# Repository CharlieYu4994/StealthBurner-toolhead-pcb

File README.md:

# StealthBurner-PCB
为 Voron Design 最新的 StealthBurner 设计的集线 PCB 板

在线 BOM 表：http://blog.charlie.moe/StealthBurner-toolhead-pcb/bom/bom

## 特点
+ 自带一个 NTC 3950 10K 的热敏电阻，可以用于测试仓温
+ 使用 StealthBurner 官方的固定孔位，可以无损兼容现有打印件
+ 使用 18 根线，比直连更省线材

## 使用

### 打样
使用「gerber」文件夹内的文件即可，建议使用 1mm 板厚，10mil 最小线宽

### 接线

1. 将 5v 连接到 LED 的 5v 电源，将 DATA 连接到 LED 信号引脚
2. 将 V_FAN 连接到你使用的风扇电源正极（两个风扇只能使用同一电压），将 PCF 和 HEF 连接到对应风扇负极
3. 将 +24v 连接到探头电源，将 P_SIG 连接到探头信号引脚
4. 将 GNDA 连接到测温接口的负极，将 CBT 和 HET 连接到对应侧温接口的正极（两个热敏电阻共地）
5. 将 A+/A-/B+/B- 连接到步进电机驱动
6. 将 HE+/HE- 连接到热端加热器接口

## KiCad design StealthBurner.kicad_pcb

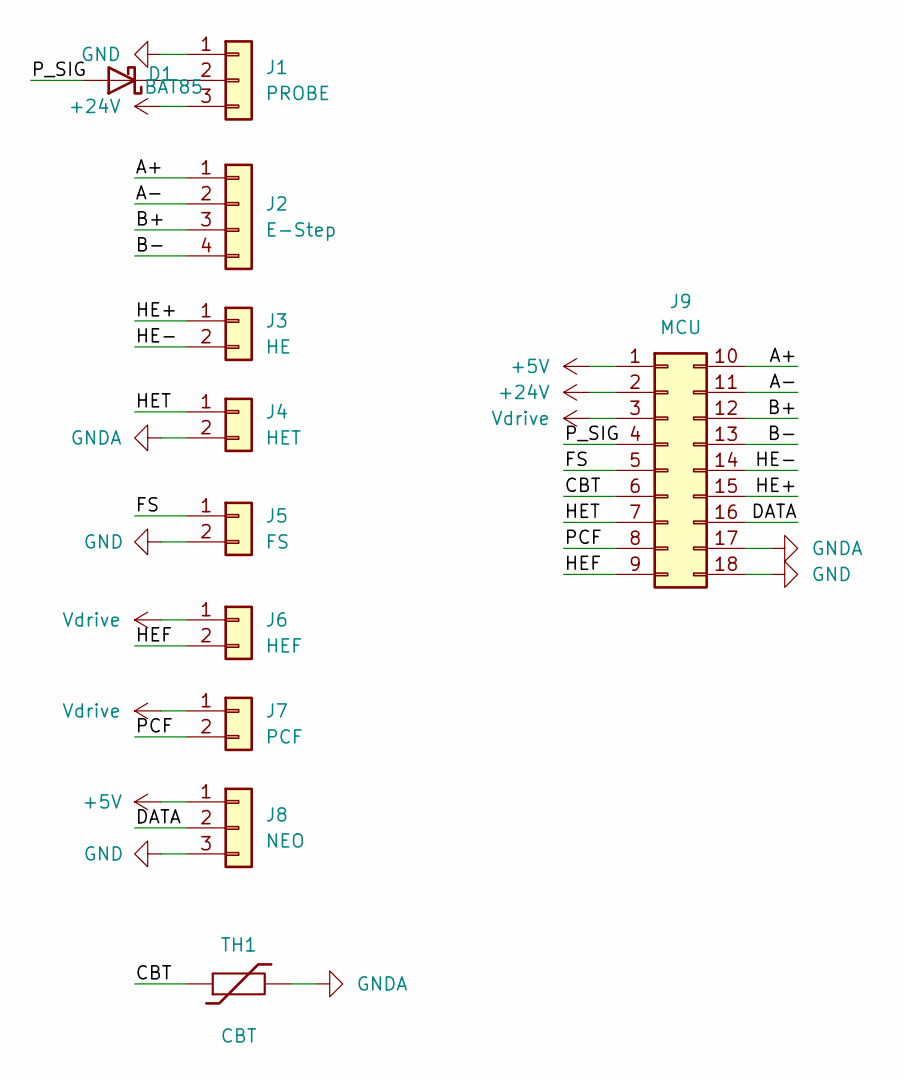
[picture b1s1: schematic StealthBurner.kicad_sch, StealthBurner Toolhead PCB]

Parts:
D1: BAT85; D_DO-35_SOD27_P2.54mm_Vertical_AnodeUp
J1: PROBE; JST_PH_B3B-PH-K_1x03_P2.00mm_Vertical
J2: E-Step; JST_PH_B4B-PH-K_1x04_P2.00mm_Vertical
J3: HE; Molex_Micro-Fit_3.0_43045-0200_2x01_P3.00mm_Horizontal
J4: HET; JST_PH_B2B-PH-K_1x02_P2.00mm_Vertical
J5: FS; JST_PH_B2B-PH-K_1x02_P2.00mm_Vertical
J6: HEF; JST_PH_B2B-PH-K_1x02_P2.00mm_Vertical
J7: PCF; JST_PH_B2B-PH-K_1x02_P2.00mm_Vertical
J8: NEO; JST_PH_B3B-PH-K_1x03_P2.00mm_Vertical
J9: MCU; Molex_Micro-Fit_3.0_43045-1800_2x09_P3.00mm_Horizontal
TH1: CBT; R_0805_2012Metric

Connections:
+5V: J8.1, J9.1
+24V: J1.3, J9.2
/A+: J2.1, J9.10
/A-: J2.2, J9.11
/B+: J2.3, J9.12
/B-: J2.4, J9.13
/CBT: J9.6, TH1.1
/DATA: J8.2, J9.16
/FS: J5.1, J9.5
/HE+: J3.1, J9.15
/HE-: J3.2, J9.14
/HEF: J6.2, J9.9
/HET: J4.1, J9.7
/PCF: J7.2, J9.8
/P_SIG: D1.2 (A), J9.4
GND: J1.1, J5.2, J8.3, J9.18
GNDA: J4.2, J9.17, TH1.2
unnamed: D1.1 (K), J1.2
Vdrive: J6.1, J7.1, J9.3

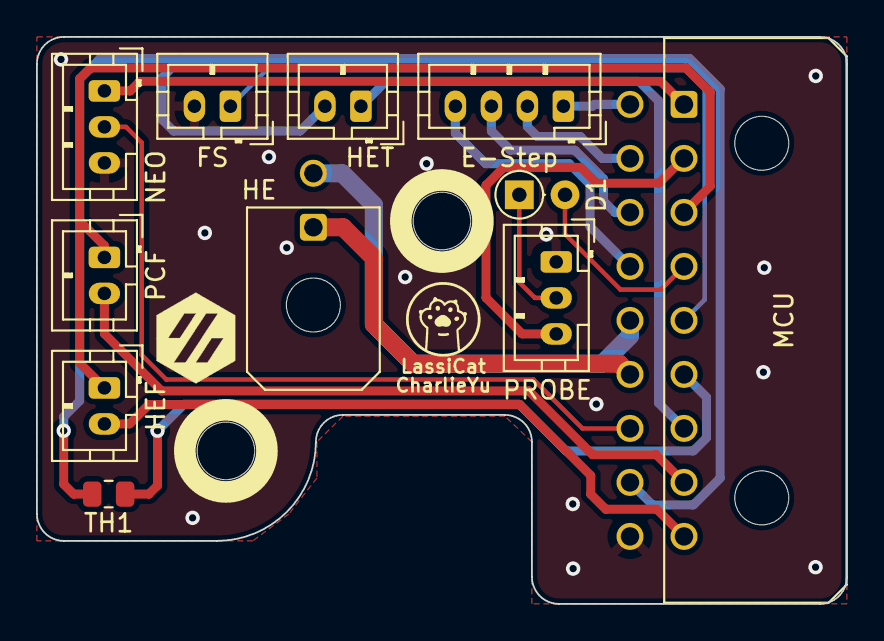
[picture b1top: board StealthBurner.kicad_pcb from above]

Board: 2 copper layers, 45.0 x 31.5 mm, 15 parts (0 on the bottom side), 19 nets.

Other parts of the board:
L1: LassiCat Organization; LassiCat_Logo
L2: Voron Hex; Voron_Logo_Hex
M1, M2: M3_hole; MountingHole_3.2mm_M3_User

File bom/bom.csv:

"Id";"Designator";"Package";"Quantity";"Designation";"Supplier and ref";
1;"J5";"JST_PH_B2B-PH-K_1x02_P2.00mm_Vertical";1;"FS";;;
2;"TH1";"R_0805_2012Metric";1;"CBT";;;
3;"J8";"JST_PH_B3B-PH-K_1x03_P2.00mm_Vertical";1;"LED";;;
4;"J6";"JST_PH_B2B-PH-K_1x02_P2.00mm_Vertical";1;"HEF";;;
5;"J9";"Molex_Micro-Fit_3.0_43045-1800_2x09_P3.00mm_Horizontal";1;"MCU";;;
6;"J2";"JST_PH_B4B-PH-K_1x04_P2.00mm_Vertical";1;"E-Step";;;
7;"J3";"Molex_Micro-Fit_3.0_43045-0200_2x01_P3.00mm_Horizontal";1;"HE";;;
8;"D1";"D_DO-35_SOD27_P2.54mm_Vertical_AnodeUp";1;"BAT85";;;
9;"J1";"JST_PH_B3B-PH-K_1x03_P2.00mm_Vertical";1;"PROBE";;;
10;"J4";"JST_PH_B2B-PH-K_1x02_P2.00mm_Vertical";1;"HET";;;
11;"J7";"JST_PH_B2B-PH-K_1x02_P2.00mm_Vertical";1;"PCF";;;

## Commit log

2022-05-22 Upload all the files
2022-05-22 Create LICENSE
2022-05-22 Update Logo
2022-05-24 修改设计规范
2022-05-29 重新设计 PCB
2022-05-29 更新到 Beta2
2022-05-29 更新 Gerber 文件以及 BOM 表
2022-05-29 修复 BOM
2022-05-31 添加丝印
2022-05-31 添加 BOM
2022-06-02 更新到 Beta2，优化探针接口位置，优化丝印
2022-06-04 微调丝印
2022-06-04 更新生产文件
2022-06-17 增加 README 文件
2022-06-17 更改线路名称
